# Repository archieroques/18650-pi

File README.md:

# 18650-pi
A GPIO (but not HAT) 18650 battery charger and boost converter for the Raspberry Pi. 

Designed Archie Roques July 2017 - released under Attribution-NonCommercial-ShareAlike 4.0 International. 

## Why?
A conversation with a fellow maker sparked this project - there was not an elegant solution available for powering a Raspberry Pi from a common 18650 battery.
Now there is!

## What?
This PCB hangs off the Raspberry Pi, and connects to the GPIO pins via a 2\*20 pin header. The header is surface mount, but there are holes in the PCB design to allow it to slot on to the Pi's existing headers before a HAT or other board is placed on top. 
It contains an 18650 battery holder, all the circuitry necessary to charge the cell, and boost its voltage to the 5v required of the Raspberry Pi. 
It also contains a switch, to swap between charging and powering mode. This means you *can't use it as a UPS type board or swap between power sources on the go. **DO NOT CONNECT USB POWER AND BATTERY POWER AT ONCE - Things will burn!***
There is a microUSB port for charging and some indicator LEDs too. 

## How?
The board uses a U1V10F5 (AKA TPS6120X) boost converter, and a common TP4056 charger chip - this is what's on most cheap LiPo charger boards. 
The battery holder used, a Keystone Electronics 1043, has a slot down the middle, intended that the battery sits flat on the board. To save space, some components are placed in this gap, so the cell probably won't sit quite flush. 
The board is made for single sided SMD assembly, with the battery holder as a through-hole part (easy to solder with just 2 large connections).
The board was designed in Eagle CAD - the files are for use with this software. I'll add gerbers, etc when the design is done and tested. 

### *NOTE: This is highly experimental! It ain't quite done, and it certainly hasn't been tested. Use it at your own risk - I am not responsibe for any damage you or it may do!*

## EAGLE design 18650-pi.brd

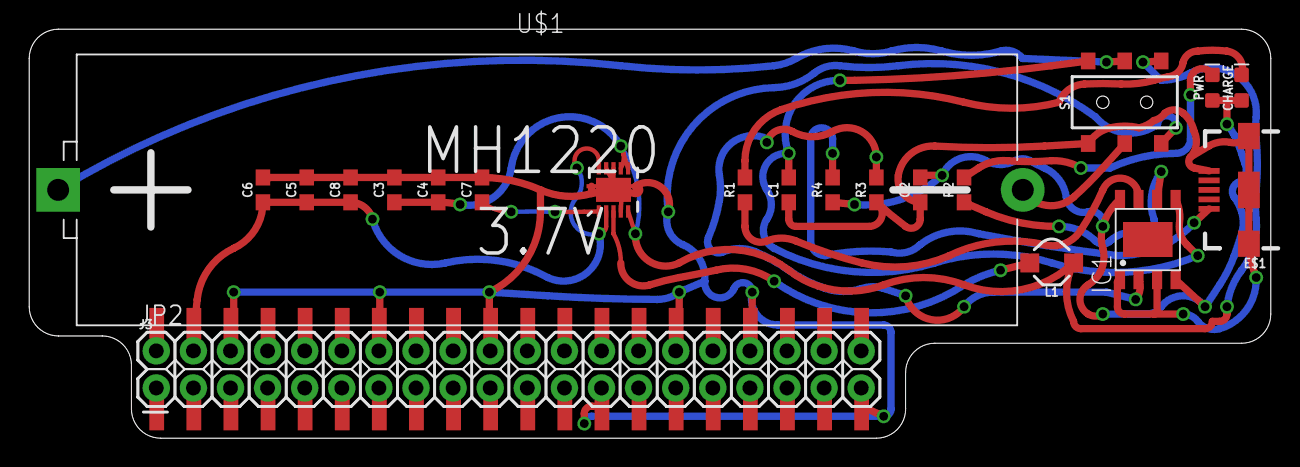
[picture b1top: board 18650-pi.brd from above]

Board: 2 copper layers, 85.0 x 28.0 mm, 22 parts (0 on the bottom side), 15 nets.

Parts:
C1, C2, C4, C5: 10uF; 0603
C3, C7, C8: 0.1uF; 0603
C6: 1.0uF; 0603
CHARGE: LED-0603
E$1: USB-B-MICRO-SMD
IC1: TP4056; SOP-8
J3: CONN_20X2; 2X20
JP2: 2X20SMD
L1: 2.2uH**; INDUCTOR_4.7UH
PWR: LED-0603
R1, R2: 1k; 0603
R3: 1.20k; 0603
R4: 0R4; 0603
S1: SWITCH_DPDT_SMD_AYZ0202
U1: TPS61200; QFN-10_PAD
U$1: BATTERY-LI-MH12210

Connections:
AGND: C1.1, C2.1, IC1.1, IC1.3, R3.1, S1.4
GND: C3.2, C4.2, C5.2, C6.2, C7.2, C8.2, JP2.6, JP2.9, JP2.14, JP2.20, JP2.25, JP2.30, JP2.34, JP2.39, S1.6, U1.4, U1.8, U1.9, U1.11, U1.12, U1.13, U1.14, U1.15
unnamed: S1.2, U$1.BAT+
unnamed: S1.5, U$1.BAT-
unnamed: CHARGE.C, R1.2
unnamed: PWR.C, R2.2
unnamed: IC1.2, R3.2
unnamed: IC1.7, R1.1
unnamed: IC1.6, R2.1
unnamed: C2.2, CHARGE.A, IC1.4, IC1.8, PWR.A, R4.1
unnamed: L1.P$2, U1.3
unnamed: C1.2, IC1.5, S1.1
unnamed: C7.1, U1.1
VCC: C5.1, C6.1, C8.1, JP2.2, JP2.4, U1.2, U1.10
VIN: C3.1, C4.1, L1.P$1, S1.3, U1.5, U1.6, U1.7

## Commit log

2017-07-01 added eagle files
2017-07-01 Update README.md
    added stuff about eagle

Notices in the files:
parts and their libraries:
SparkFun-Capacitors: Licensing: Creative Commons ShareAlike 4.0 International - https://creativecommons.org/licenses/by-sa/4.0
diy-modules: Released under the Creative Commons Attribution 4.0 International License: http://creativecommons.org/licenses/by/4.0
